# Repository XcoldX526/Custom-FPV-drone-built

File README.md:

# 🚁 Custom FPV Acro Drone Build

> A fully custom FPV acro drone featuring a hand-designed PCB, 3D-printed frame, and from-scratch hardware design — built for the [Hack Club Stardance](https://hackclub.com/) grant program.

---

## 📖 Project Overview

This project is a custom-built FPV (First Person View) acro drone, designed entirely from scratch by a team of two. The build covers everything from PCB design in KiCad to 3D-printed frame components modelled in OnShape. Rather than buying an off-the-shelf flight controller, we designed our own — a custom PCB centred around the **STM32F722** microcontroller paired with a **MAX7456** OSD chip and an **MPU-6050** IMU, giving us full control over the hardware stack.

The project went through two major PCB revisions and a complete rethink of the drone type mid-development, making this a genuine engineering challenge from start to finish.

---

## 👥 Team

| Name | Role |
|------|------|
| Me (Author) | PCB design, schematic, component layout, routing |
| Best Friend | 3D frame design (STL files, OnShape) |

---

## ⏱️ Time Log

> **Note on time tracking:** Hackatime couldn't be used as the `/hack` Slack command failed to respond (see screenshot below). Time was tracked manually as accurately and honestly as possible.

| Task | Person | Hours | Notes |
|------|--------|-------|-------|
| Learning KiCad (PCB software) | Me | 2.5 hrs | First time using KiCad — learning footprints, schematic editor, PCB layout tools |
| PCB Version 1 — Design & Layout | Me | 4.5 hrs | Designed for a different drone type; pivoted to acro drone after completion |
| PCB Version 2 — Redesign & Routing | Me | 5.0 hrs | Full redesign for acro drone; unfamiliar territory, significant routing challenges |
| 3D Frame Design (STL) | Best Friend | 8.0 hrs | OnShape was familiar but getting drone dimensions accurate was far more difficult than expected |
| **Total** | | **20.0 hrs** | |

---

## 🔧 Hardware Design

### PCB — Custom Flight Controller

The PCB was designed in **KiCad** and went through two full revisions.

#### Key Components
- **STM32F722** — Main flight controller MCU
- **MPU-6050** — 6-axis IMU (gyroscope + accelerometer) for flight stabilisation
- **MAX7456** — OSD (On-Screen Display) chip for FPV video overlay
- **ESP32-C3-WROOM-02** — Wi-Fi/Bluetooth module (V1 design)
- Connectors: `Conn_01x04_Pin`, `Conn_01x08_Pin`, `Conn_01x03_Pin`
- 4× M2.2mm mounting holes for frame attachment

#### PCB Revision History

**Version 1**
- Designed around the ESP32-C3-WROOM-02 as the main module
- Intended for a different drone form factor
- After completing this version, we made the decision to pivot to a proper acro drone build
- Features keep-out zone for the ESP32 antenna

**Version 2 (Current)**
- Full redesign around the STM32F722 for proper acro flight controller functionality
- Integrated MPU-6050 IMU for accurate flight data
- Added MAX7456 OSD chip
- 121 pads, 28 vias, 168 track segments across 81 nets
- 1 unrouted connection remaining at time of documentation

#### PCB Stats (V2 Final)
```
Pads:           121
Vias:            28
Track Segments: 168
Nets:            81
Unrouted:         1
```

### 3D Frame — Custom STL Design

The drone frame was designed by my best friend using **OnShape**. Despite being familiar with OnShape as a tool, designing a drone frame proved significantly more challenging than expected — getting the dimensions accurate for motor mounting, prop clearance, and PCB fitment required many iterations over 8 hours of focused work.

---

## 🗂️ Project Structure

```
custom-fpv-drone/
├── README.md
├── pcb/
│   ├── hackaton-fpv-drone.kicad_pcb     # KiCad PCB file (V2)
│   ├── hackaton-fpv-drone.kicad_sch     # Schematic
│   └── ...
├── stl/
│   └── drone-frame.stl                  # 3D printed frame (OnShape export)
└── images/
    ├── pcb-v2-layout.png                # Final PCB layout in KiCad
    ├── pcb-v1-layout.png                # V1 PCB layout
    ├── pcb-v1-schematic.png             # V1 schematic view
    ├── pcb-v1-3d.png                    # V1 component placement
    └── hacktime-issue.png               # Evidence of Hackatime tracking issue
```

---

## 🖼️ Screenshots & Evidence

### Final PCB (V2) — KiCad PCB Editor
The completed V2 PCB layout showing the STM32F722 at the centre, surrounding connectors, IMU placement, and OSD chip. The board features 4 mounting holes and organised track routing across front and back copper layers.

### Version 1 PCB — ESP32-C3 Based Design
The original PCB design built around the ESP32-C3-WROOM-02 module, including the required keep-out zone for the antenna. This was designed for a different drone form factor before the pivot to acro.

### Schematic (V1)
The KiCad schematic showing the ESP32-C3 connected to the MPU-6050 IMU, connectors, and supporting passives.

### Hackatime Issue — Evidence
Screenshot showing the `/hack` Slack command failing with the error: *"the app did not respond"*. This is why time was logged manually.

---

## 🛠️ Tools Used

| Tool | Purpose |
|------|---------|
| KiCad 8.x | PCB schematic and layout design |
| OnShape | 3D frame modelling and STL export |
| Hack Club Slack | Team communication and project logging |
| Hackatime | Attempted time tracking (see issues above) |

---

## 🚧 Current Status & Next Steps

- [x] PCB V1 designed and completed
- [x] Pivoted to acro drone form factor
- [x] PCB V2 schematic completed
- [x] PCB V2 layout completed (1 unrouted net remaining)
- [x] 3D frame STL designed
- [ ] Complete final PCB routing (1 net)
- [ ] Order PCB from manufacturer
- [ ] Print frame STL
- [ ] Source and assemble components
- [ ] Flash firmware and test

---

## 💡 Reflections

This project pushed both of us well outside our comfort zones. Learning KiCad from scratch, pivoting mid-project when we decided acro was the right form factor, and wrestling with dimension constraints in OnShape were all genuine challenges. Hackatime didn't cooperate, but we tracked our time as honestly as we could and have screenshot evidence of the tooling failure.

The 20 hours logged represents real, focused engineering work — not just sitting in front of a screen.

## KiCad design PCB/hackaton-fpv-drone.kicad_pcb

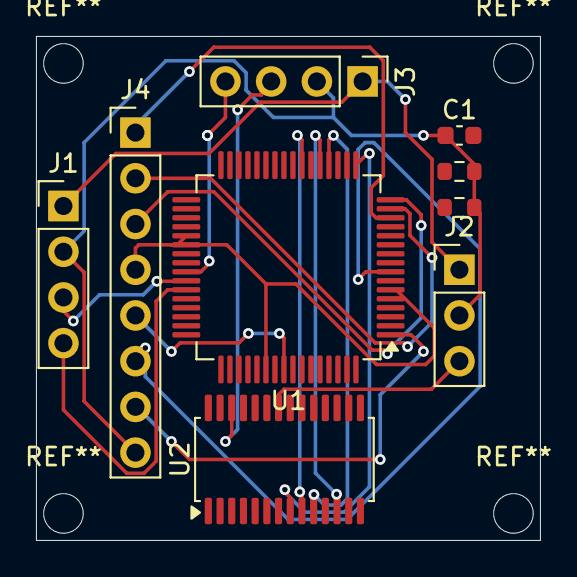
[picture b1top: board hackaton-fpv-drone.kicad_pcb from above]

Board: 2 copper layers, 28.0 x 28.0 mm, 9 parts (0 on the bottom side), 18 nets.

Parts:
C1: C; C_0603_1608Metric
J1, J3: Conn_01x04_Pin; PinHeader_1x04_P2.54mm_Vertical
J2: Conn_01x03_Pin; PinHeader_1x03_P2.54mm_Vertical
J4: Conn_01x08_Pin; PinHeader_1x08_P2.54mm_Vertical
R1, R2: 1k; R_0603_1608Metric
U1: STM32F722RET6; LQFP-64_10x10mm_P0.5mm
U2: MAX7456EUI_; TSSOP-28_4.4x9.7mm_P0.65mm

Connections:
+3.3V: C1.1, J1.2, J2.2, J3.2, J4.8, R1.2, R2.2
+5V: J1.1, J2.1, J3.1
unnamed: J1.3, U1.42 (PA9)
unnamed: J1.4, U1.43 (PA10)
unnamed: J2.3, U2.22 (VIN)
unnamed: J3.3, U2.26 (VOUT)
unnamed: J3.4, U1.41 (PA8)
unnamed: J4.1, U1.14 (PA0-WKUP)
unnamed: J4.2, U1.15 (PA1)
unnamed: J4.3, U1.16 (PA2)
unnamed: J4.4, U1.5 (PH0-OSC_IN), U1.6 (PH1-OSC_OUT), U1.37 (PC6), U1.38 (PC7), U1.54 (PD2)
unnamed: J4.5, U1.56 (PB4(~JTRST))
unnamed: J4.6, U1.8 (PC0)
unnamed: J4.7, U1.1 (VBAT)
unnamed: U1.17 (PA3), U2.8 (~CS)
unnamed: U1.20 (PA4), U2.10 (SCLK)
unnamed: U1.21 (PA5), U2.12 (LOS)
unnamed: U1.23 (PA7), U2.9 (SDIN)
